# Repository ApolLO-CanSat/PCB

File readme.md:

# Team ApolLO's CanSat PCBs
The mainboard features:
- **RP2350A** MCU 
- **W25Q128JVPIQ** flash memory
- **Waveshare 23721** for GPS signal
- **RFM98W 433MHz** LoRa module
- **MPU-6050** gyroscope and accelerometer
- **BMP 280** barometer and thermometer
- **USB-C connector**
- **BOOTSEL** and **RESET** buttons
- Status **LED**
- **Buzzer** for easier recovery
\

\

\
[Schematics in PDF file](https://github.com/ApolLO-CanSat/PCB/blob/main/schematics/CanSat.pdf)
\

\
[PCB schematic in PDF file](https://github.com/ApolLO-CanSat/PCB/blob/main/schematics/CanSatPCB.pdf)
---
## BOM
|Id|Designator|Footprint|Quantity|Designation|
|-|-|-|-|-|
|1|R5,R24,R12,R1,R21,R23,R22|R_0805_2012Metric|7|10K|
|2|R26,R25|R_0402_1005Metric|2|4.7K|
|3|C25|C_0805_2012Metric|1|10nF|
|4|R4,R3|R_0805_2012Metric|2|27|
|5|J8|PinHeader_1x02_P2.00mm_Vertical|1|Conn_01x02_Pin|
|6|L1|AOTAB201610S3R3101T|1|3.3u|
|7|D2|LED_0402_1005Metric|1|RED|
|8|U5|RP2350-QFN-60-1EP_7x7_P0.4mm_EP3.4x3.4mm_ThermalVias|1|RP2350_60QFN|
|9|C16,C9,C8,C11|C_0402_1005Metric|4|4.7uF|
|10|C20,C3,C4,C10,C22,C12,C7,C1,C5,C6,C2|C_0402_1005Metric|11|100nF|
|11|C24,C23|C_0402_1005Metric|2|15pF|
|12|C30,C15,C17,C32,C27,C28,C19|C_0805_2012Metric|7|100nF|
|13|BZ1|CMT-4023S|1|Buzzer|
|14|J1|USB_C_Receptacle_Amphenol_12401610E4-2A|1|USB_C_Receptacle|
|15|C31|C_0805_2012Metric|1|22u|
|16|SW2,SW1,SW3|SW_Push_1P1T_NO_Vertical_Wuerth_434133025816|3|SW_Push|
|17|IC1|SON127P600X500X80-9N-D|1|W25Q128JVPIQ|
|18|C21,C13|C_0805_2012Metric|2|1uF|
|19|D1|MMBT2907AM3T5G|1|ESD7L5.0DT5G|
|20|D4,D3|D_SOD-123|2|MBR0530T1G|
|21|R11,R10|R_0805_2012Metric|2|5.1K|
|22|J10|PinHeader_1x04_P2.00mm_Vertical|1|Conn_01x04_Pin|
|23|R18|R_0805_2012Metric|1|100|
|24|J2|SMA_Amphenol_901-144_Vertical|1|Conn_Coaxial|
|25|R17|R_0402_1005Metric|1|10K|
|26|R20|R_0402_1005Metric|1|33|
|27|U3|PinHeader_1x05_P1.00mm_Vertical|1|Waveshare23721|
|28|C18|C_0805_2012Metric|1|2.2nF|
|29|U8|Bosch_LGA-8_2x2.5mm_P0.65mm_ClockwisePinNumbering|1|BMP280|
|30|R2,R14,R13|R_0805_2012Metric|3|1K|
|31|Y1|ABM8272T3|1|ABM8272T3|
|32|C29|C_0805_2012Metric|1|2.2uF|
|33|Q1|SOT-23|1|BSS138|
|34|U9|PSON50P200X300X50-9N|1|APS6404L-3SQR-ZR|
|35|J6|PinHeader_2x03_P1.00mm_Vertical|1|Conn_01x06_Pin|
|36|R15|R_0805_2012Metric|1|220|
|37|J7|JST_SH_BM03B-SRSS-TB_1x03-1MP_P1.00mm_Vertical|1|Conn_01x03_Pin|
|38|R16|R_0805_2012Metric|1|DNC|
|39|J5|JST_PH_B2B-PH-K_1x02_P2.00mm_Vertical|1|Screw_Terminal_01x02|
|40|J9|JST_SH_BM03B-SRSS-TB_1x03-1MP_P1.00mm_Vertical|1|Conn_01x02_Pin|
|41|J11|JST_PH_B3B-PH-K_1x03_P2.00mm_Vertical|1|Conn_01x03_Socket|
|42|J3|JST_SH_BM06B-SRSS-TB_1x06-1MP_P1.00mm_Vertical|1|Conn_01x06_Socket|
|43|U4|HOPERF_RFM9XW_SMD|1|RFM98W-433S2|
|44|C14|C_0805_2012Metric|1|DNP|
|45|U1|InvenSense_QFN-24_4x4mm_P0.5mm|1|MPU-6050|
|46|J4|JST_PH_B2B-PH-K_1x02_P2.00mm_Vertical|1|Conn_01x02_Pin|
|47|R19|R_0402_1005Metric|1|1K|

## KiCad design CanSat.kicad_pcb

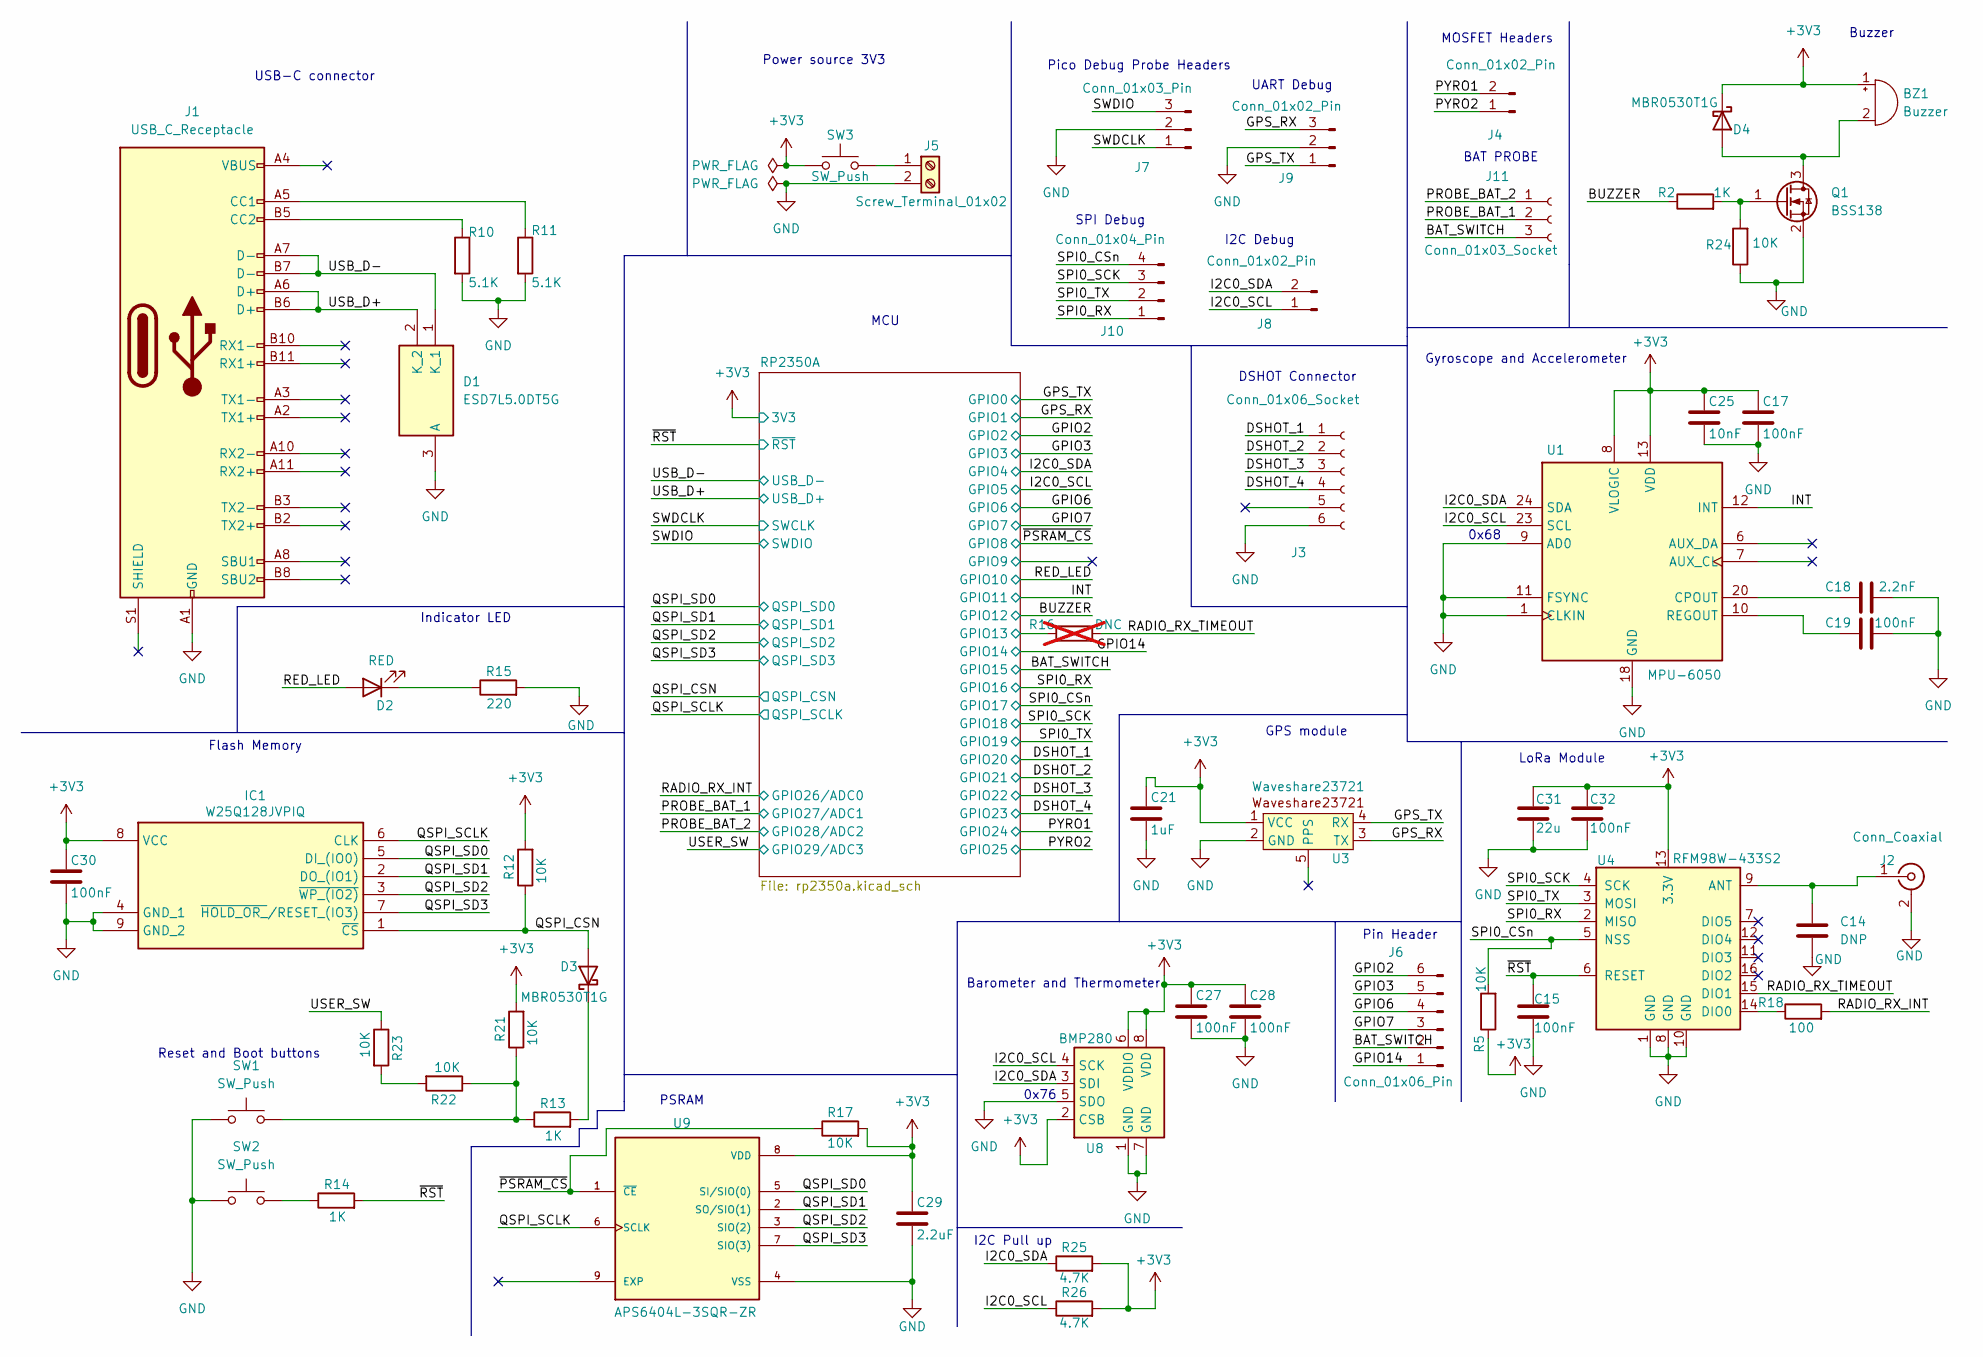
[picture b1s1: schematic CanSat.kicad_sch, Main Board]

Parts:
BZ1: Buzzer; CMT-4023S
C14: DNP; C_0805_2012Metric
C15, C17, C19, C27, C28, C30, C32: 100nF; C_0805_2012Metric
C18: 2.2nF; C_0805_2012Metric
C21: 1uF; C_0805_2012Metric
C25: 10nF; C_0805_2012Metric
C29: 2.2uF; C_0805_2012Metric
C31: 22u; C_0805_2012Metric
D1: ESD7L5.0DT5G; MMBT2907AM3T5G; Mouser Part Number 863-ESD7L5.0DT5G
D2: RED; LED_0402_1005Metric
D3, D4: MBR0530T1G; D_SOD-123
IC1: W25Q128JVPIQ; SON127P600X500X80-9N-D; Mouser Part Number 454-W25Q128JVPIQ
J1: USB_C_Receptacle; USB_C_Receptacle_Amphenol_12401610E4-2A
J2: Conn_Coaxial; SMA_Amphenol_901-144_Vertical
J3: Conn_01x06_Socket; JST_SH_BM06B-SRSS-TB_1x06-1MP_P1.00mm_Vertical
J4: Conn_01x02_Pin; JST_PH_B2B-PH-K_1x02_P2.00mm_Vertical
J5: Screw_Terminal_01x02; JST_PH_B2B-PH-K_1x02_P2.00mm_Vertical
J6: Conn_01x06_Pin; PinHeader_2x03_P1.00mm_Vertical
J7: Conn_01x03_Pin; JST_SH_BM03B-SRSS-TB_1x03-1MP_P1.00mm_Vertical
J8: Conn_01x02_Pin; PinHeader_1x02_P2.00mm_Vertical
J9: Conn_01x02_Pin; JST_SH_BM03B-SRSS-TB_1x03-1MP_P1.00mm_Vertical
J10: Conn_01x04_Pin; PinHeader_1x04_P2.00mm_Vertical
J11: Conn_01x03_Socket; JST_PH_B3B-PH-K_1x03_P2.00mm_Vertical
Q1: BSS138; SOT-23
R2, R13, R14: 1K; R_0805_2012Metric
R5, R12, R21, R22, R23, R24: 10K; R_0805_2012Metric
R10, R11: 5.1K; R_0805_2012Metric
R15: 220; R_0805_2012Metric
R16: DNC; R_0805_2012Metric; not fitted
R17: 10K; R_0402_1005Metric
R18: 100; R_0805_2012Metric
R25, R26: 4.7K; R_0402_1005Metric
SW1, SW2, SW3: SW_Push; SW_Push_1P1T_NO_Vertical_Wuerth_434133025816
U1: MPU-6050; InvenSense_QFN-24_4x4mm_P0.5mm
U3: Waveshare23721; PinHeader_1x05_P1.00mm_Vertical
U4: RFM98W-433S2; HOPERF_RFM9XW_SMD
U8: BMP280; Bosch_LGA-8_2x2.5mm_P0.65mm_ClockwisePinNumbering
U9: APS6404L-3SQR-ZR; PSON50P200X300X50-9N; PARTREV 2.3

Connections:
+3V3: BZ1.1 (+), C17.1, C21.1, C25.1, C27.1, C28.1, C29.1, C30.1, C31.1, C32.1, D4.1 (K), IC1.8 (VCC), R5.1, R12.2, R17.2, R21.2, R25.2, R26.2, SW3.1, U1.8 (VLOGIC), U1.13 (VDD), U3.1 (VCC), U4.13 (3.3V), U8.2 (CSB), U8.6 (VDDIO), U8.8 (VDD), U9.8 (VDD); also elsewhere on the board
/BAT_SWITCH: J6.2, J11.3; also elsewhere on the board
/BUZZER: R2.1; also elsewhere on the board
/DSHOT_1: J3.1; also elsewhere on the board
/DSHOT_2: J3.2; also elsewhere on the board
/DSHOT_3: J3.3; also elsewhere on the board
/DSHOT_4: J3.4; also elsewhere on the board
/GPIO2: J6.6; also elsewhere on the board
/GPIO3: J6.5; also elsewhere on the board
/GPIO6: J6.4; also elsewhere on the board
/GPIO7: J6.3; also elsewhere on the board
/GPIO14: J6.1; also elsewhere on the board
/GPS_RX: J9.3, U3.3 (TX); also elsewhere on the board
/GPS_TX: J9.1, U3.4 (RX); also elsewhere on the board
/I2C0_SCL: J8.1, R26.1, U1.23 (SCL), U8.4 (SCK); also elsewhere on the board
/I2C0_SDA: J8.2, R25.1, U1.24 (SDA), U8.3 (SDI); also elsewhere on the board
/INT: U1.12 (INT); also elsewhere on the board
/PROBE_BAT_1: J11.2; also elsewhere on the board
/PROBE_BAT_2: J11.1; also elsewhere on the board
/PYRO1: J4.2; also elsewhere on the board
/PYRO2: J4.1; also elsewhere on the board
/QSPI_CSN: D3.2 (A), IC1.1 (~CS), R12.1; also elsewhere on the board
/QSPI_SCLK: IC1.6 (CLK), U9.6 (SCLK); also elsewhere on the board
/QSPI_SD0: IC1.5 (DI_(IO0)), U9.5 (SI/SIO(0)); also elsewhere on the board
/QSPI_SD1: IC1.2 (DO_(IO1)), U9.2 (SO/SIO(1)); also elsewhere on the board
/QSPI_SD2: IC1.3 (~WP_(IO2)), U9.3 (SIO(2)); also elsewhere on the board
/QSPI_SD3: IC1.7 (~HOLD_OR_/RESET_(IO3)), U9.7 (SIO(3)); also elsewhere on the board
/RADIO_RX_INT: R18.2; also elsewhere on the board
/RADIO_RX_TIMEOUT: R16.2, U4.15 (DIO1)
/RED_LED: D2.2 (A); also elsewhere on the board
/RP2350A/GPIO13: R16.1; also elsewhere on the board
/SPI0_CSn: J10.4, R5.2, U4.5 (NSS); also elsewhere on the board
/SPI0_RX: J10.1, U4.2 (MISO); also elsewhere on the board
/SPI0_SCK: J10.3, U4.4 (SCK); also elsewhere on the board
/SPI0_TX: J10.2, U4.3 (MOSI); also elsewhere on the board
/SWDCLK: J7.1; also elsewhere on the board
/SWDIO: J7.3; also elsewhere on the board
/USB_D+: D1.2 (K_2), J1.A6 (D+), J1.B6 (D+); also elsewhere on the board
/USB_D-: D1.1 (K_1), J1.A7 (D-), J1.B7 (D-); also elsewhere on the board
/USER_SW: R23.1; also elsewhere on the board
/~PSRAM_CS: R17.1, U9.1 (~CE); also elsewhere on the board
/~RST: C15.1, R14.2, U4.6 (RESET); also elsewhere on the board
GND: C14.1, C15.2, C17.2, C18.2, C19.2, C21.2, C25.2, C27.2, C28.2, C29.2, C30.2, C31.2, C32.2, D1.3 (A), IC1.4 (GND_1), IC1.9 (GND_2), J1.A1 (GND), J1.A12 (GND), J1.B1 (GND), J1.B12 (GND), J2.2 (Ext), J3.6, J5.2, J7.2, J9.2, Q1.2 (S), R10.2, R11.2, R15.2, R24.1, SW1.1, SW2.1, U1.1 (CLKIN), U1.9 (AD0), U1.11 (FSYNC), U1.18 (GND), U3.2 (GND), U4.1 (GND), U4.8 (GND), U4.10 (GND), U8.1 (GND), U8.5 (SDO), U8.7 (GND), U9.4 (VSS); also elsewhere on the board
unnamed: BZ1.2 (-), D4.2 (A), Q1.3 (D)
unnamed: D2.1 (K), R15.1
unnamed: D3.1 (K), R13.2
unnamed: J1.A5 (CC1), R11.1
unnamed: J1.B5 (CC2), R10.1
unnamed: C14.2, J2.1 (In), U4.9 (ANT)
unnamed: J5.1, SW3.2
unnamed: Q1.1 (G), R2.2, R24.2
unnamed: R13.1, R21.1, R22.1, SW1.2
unnamed: R14.1, SW2.2
unnamed: R22.2, R23.2
unnamed: C18.1, U1.20 (CPOUT)
unnamed: C19.1, U1.10 (REGOUT)
unnamed: R18.1, U4.14 (DIO0)

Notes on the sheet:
I2C Pull up
0x68
BAT PROBE
UART Debug
Buzzer
Gyroscope and Accelerometer
Reset and Boot buttons
GPS module
LoRa Module
MOSFET Headers
Power source 3V3
Pin Header
I2C Debug
PSRAM
Pico Debug Probe Headers
MCU
0x76
SPI Debug
Barometer and Thermometer
USB-C connector
Indicator LED
Flash Memory
DSHOT Connector

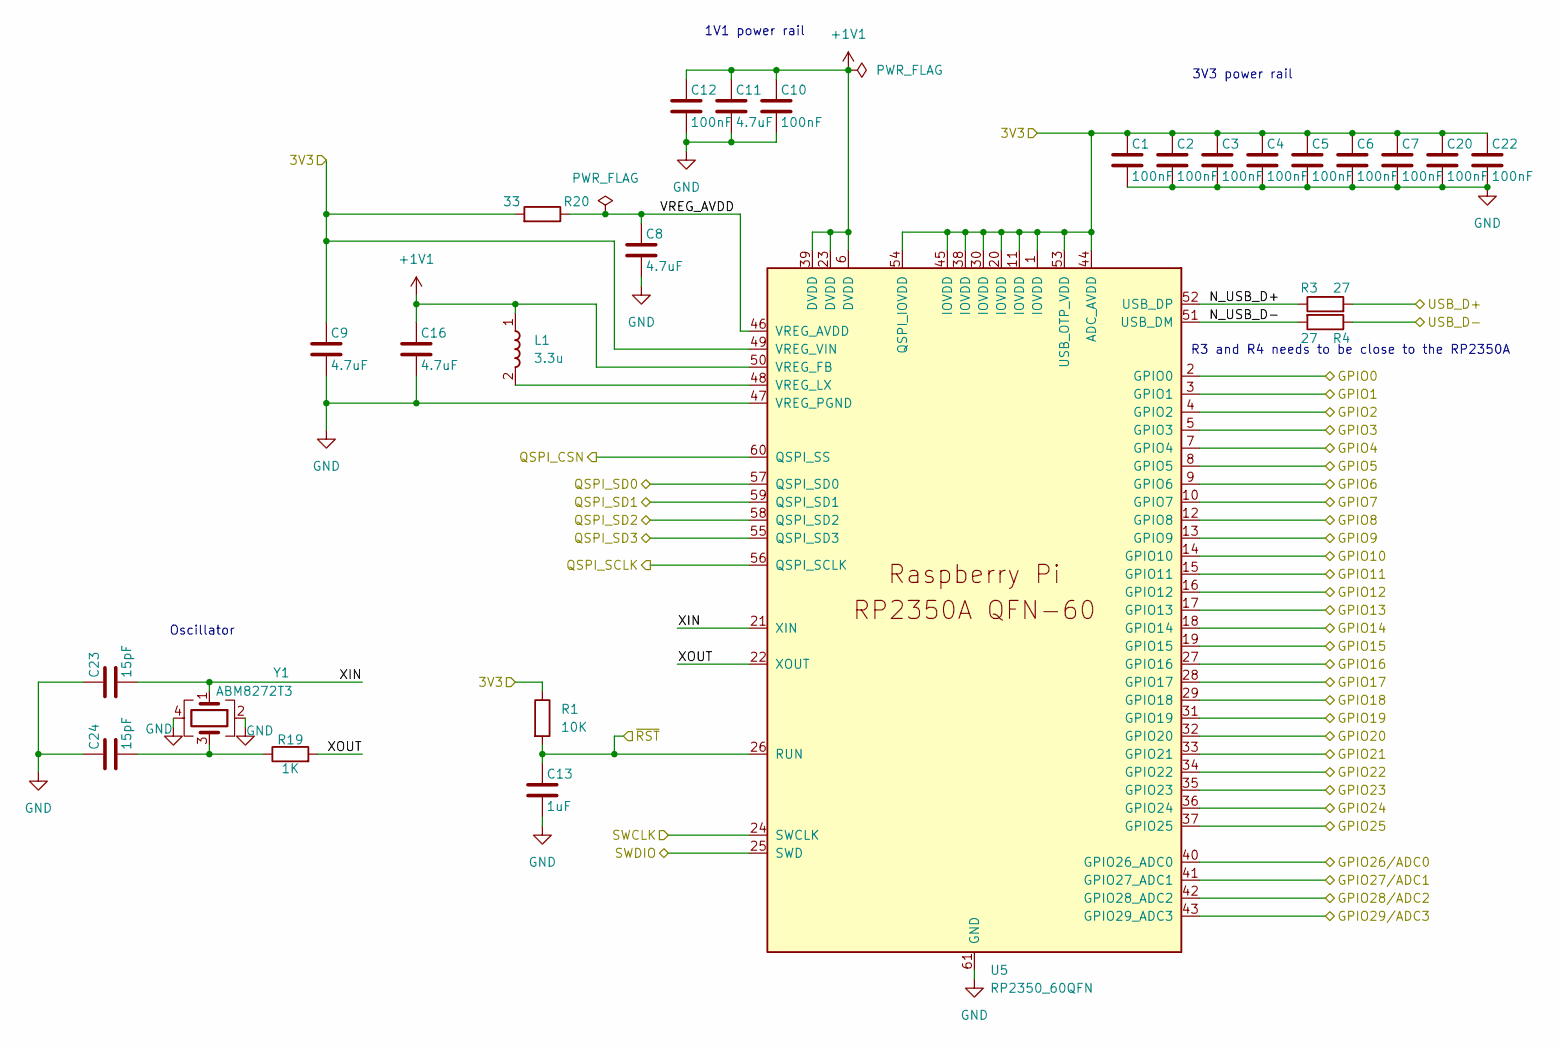
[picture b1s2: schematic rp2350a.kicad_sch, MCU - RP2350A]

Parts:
C1, C2, C3, C4, C5, C6, C7, C10, C12, C20, C22: 100nF; C_0402_1005Metric
C8, C9, C11, C16: 4.7uF; C_0402_1005Metric
C13: 1uF; C_0805_2012Metric
C23, C24: 15pF; C_0402_1005Metric
L1: 3.3u; AOTAB201610S3R3101T; Mouser Part Number 815-AB201610S3R3101T
R1: 10K; R_0805_2012Metric
R3, R4: 27; R_0805_2012Metric
R19: 1K; R_0402_1005Metric
R20: 33; R_0402_1005Metric
U5: RP2350_60QFN; RP2350-QFN-60-1EP_7x7_P0.4mm_EP3.4x3.4mm_ThermalVias
Y1: ABM8272T3

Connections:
+1V1: C10.1, C11.1, C12.1, C16.1, L1.1, U5.6 (DVDD), U5.23 (DVDD), U5.39 (DVDD), U5.50 (VREG_FB)
+3V3: C1.1, C2.1, C3.1, C4.1, C5.1, C6.1, C7.1, C9.1, C20.1, C22.1, R1.1, R20.2, U5.1 (IOVDD), U5.11 (IOVDD), U5.20 (IOVDD), U5.30 (IOVDD), U5.38 (IOVDD), U5.44 (ADC_AVDD), U5.45 (IOVDD), U5.49 (VREG_VIN), U5.53 (USB_OTP_VDD), U5.54 (QSPI_IOVDD); also elsewhere on the board
/BAT_SWITCH: U5.19 (GPIO15); also elsewhere on the board
/BUZZER: U5.16 (GPIO12); also elsewhere on the board
/DSHOT_1: U5.32 (GPIO20); also elsewhere on the board
/DSHOT_2: U5.33 (GPIO21); also elsewhere on the board
/DSHOT_3: U5.34 (GPIO22); also elsewhere on the board
/DSHOT_4: U5.35 (GPIO23); also elsewhere on the board
/GPIO2: U5.4 (GPIO2); also elsewhere on the board
/GPIO3: U5.5 (GPIO3); also elsewhere on the board
/GPIO6: U5.9 (GPIO6); also elsewhere on the board
/GPIO7: U5.10 (GPIO7); also elsewhere on the board
/GPIO14: U5.18 (GPIO14); also elsewhere on the board
/GPS_RX: U5.3 (GPIO1); also elsewhere on the board
/GPS_TX: U5.2 (GPIO0); also elsewhere on the board
/I2C0_SCL: U5.8 (GPIO5); also elsewhere on the board
/I2C0_SDA: U5.7 (GPIO4); also elsewhere on the board
/INT: U5.15 (GPIO11); also elsewhere on the board
/PROBE_BAT_1: U5.41 (GPIO27_ADC1); also elsewhere on the board
/PROBE_BAT_2: U5.42 (GPIO28_ADC2); also elsewhere on the board
/PYRO1: U5.36 (GPIO24); also elsewhere on the board
/PYRO2: U5.37 (GPIO25); also elsewhere on the board
/QSPI_CSN: U5.60 (QSPI_SS); also elsewhere on the board
/QSPI_SCLK: U5.56 (QSPI_SCLK); also elsewhere on the board
/QSPI_SD0: U5.57 (QSPI_SD0); also elsewhere on the board
/QSPI_SD1: U5.59 (QSPI_SD1); also elsewhere on the board
/QSPI_SD2: U5.58 (QSPI_SD2); also elsewhere on the board
/QSPI_SD3: U5.55 (QSPI_SD3); also elsewhere on the board
/RADIO_RX_INT: U5.40 (GPIO26_ADC0); also elsewhere on the board
/RED_LED: U5.14 (GPIO10); also elsewhere on the board
/RP2350A/GPIO9: U5.13 (GPIO9)
/RP2350A/GPIO13: U5.17 (GPIO13); also elsewhere on the board
/RP2350A/N_USB_D+: R3.1, U5.52 (USB_DP)
/RP2350A/N_USB_D-: R4.2, U5.51 (USB_DM)
/RP2350A/VREG_AVDD: C8.1, R20.1, U5.46 (VREG_AVDD)
/RP2350A/XIN: C23.2, U5.21 (XIN), Y1.1
/RP2350A/XOUT: R19.2, U5.22 (XOUT)
/SPI0_CSn: U5.28 (GPIO17); also elsewhere on the board
/SPI0_RX: U5.27 (GPIO16); also elsewhere on the board
/SPI0_SCK: U5.29 (GPIO18); also elsewhere on the board
/SPI0_TX: U5.31 (GPIO19); also elsewhere on the board
/SWDCLK: U5.24 (SWCLK); also elsewhere on the board
/SWDIO: U5.25 (SWD); also elsewhere on the board
/USB_D+: R3.2; also elsewhere on the board
/USB_D-: R4.1; also elsewhere on the board
/USER_SW: U5.43 (GPIO29_ADC3); also elsewhere on the board
/~PSRAM_CS: U5.12 (GPIO8); also elsewhere on the board
/~RST: C13.1, R1.2, U5.26 (RUN); also elsewhere on the board
GND: C1.2, C2.2, C3.2, C4.2, C5.2, C6.2, C7.2, C8.2, C9.2, C10.2, C11.2, C12.2, C13.2, C16.2, C20.2, C22.2, C23.1, C24.1, U5.47 (VREG_PGND), U5.61 (GND), Y1.2, Y1.4; also elsewhere on the board
unnamed: C24.2, R19.1, Y1.3
unnamed: L1.2, U5.48 (VREG_LX)

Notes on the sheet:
1V1 power rail
R3 and R4 needs to be close to the RP2350A
3V3 power rail
Oscillator

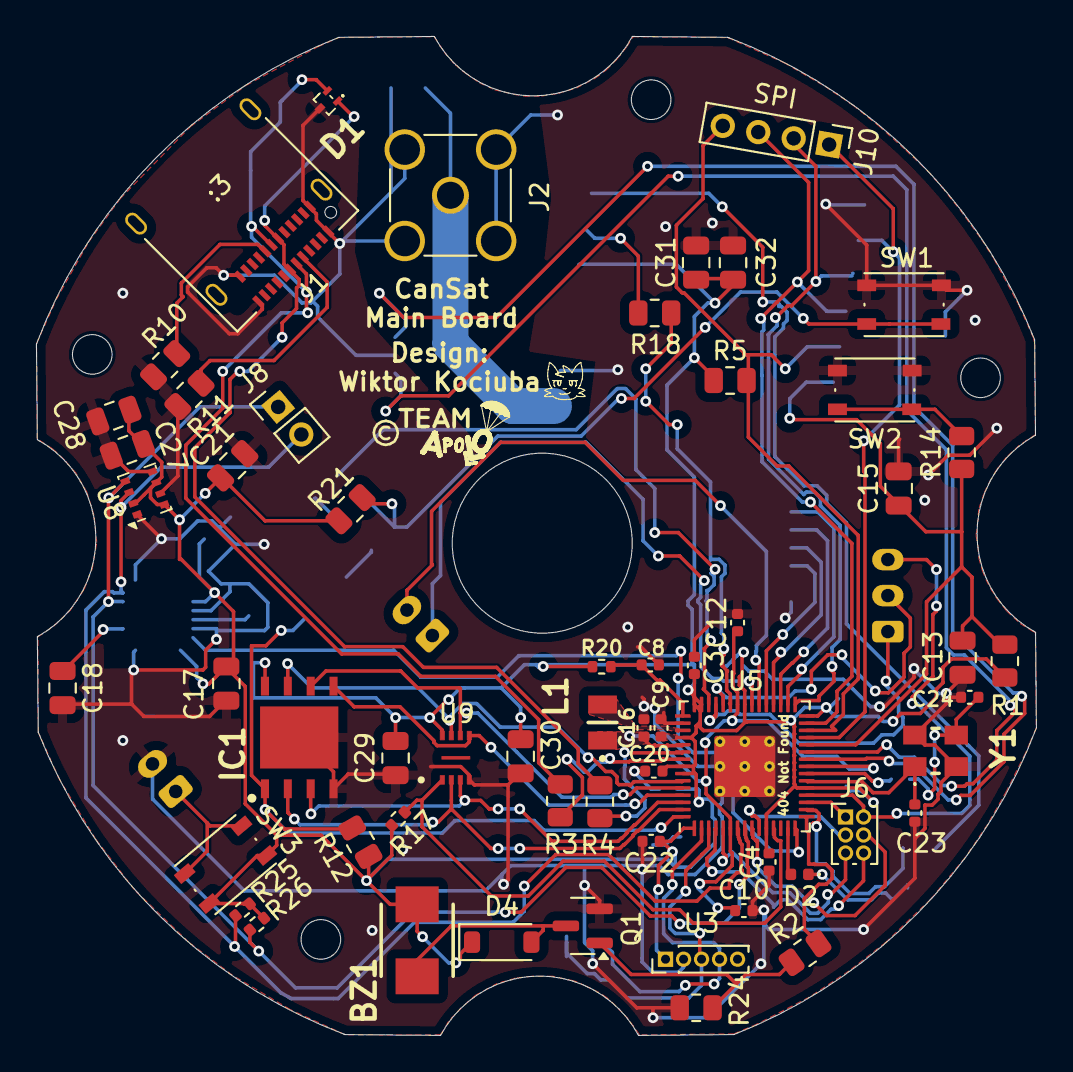
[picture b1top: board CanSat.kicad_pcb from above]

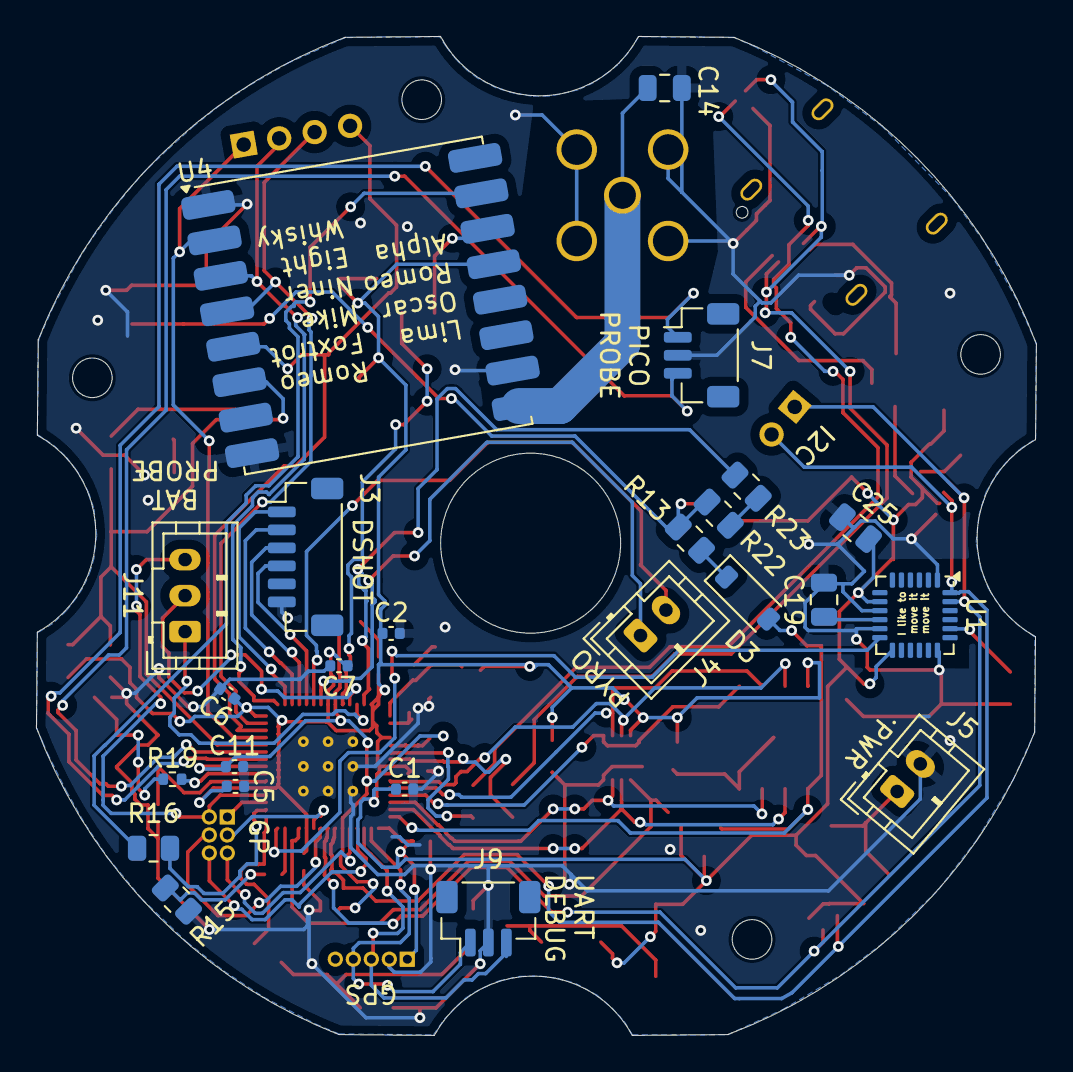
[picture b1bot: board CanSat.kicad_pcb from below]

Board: 2 copper layers, 55.6 x 55.5 mm, 84 parts (24 on the bottom side), 65 nets.

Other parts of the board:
M2, M2#2: MountingHole_2.2mm_M2

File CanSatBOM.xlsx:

Id | Designator | Footprint | Quantity | Value | Manufacturer | Mfg Part # | Package | Type
1 | R4,R7,R3,R8,R9,R6,R5 | R_0805_2012Metric | 7 | 27 OHM | any available | any available | 0805(2012M) | SMD
2 | J8,J9,J4 | PinHeader_1x02_P1.00mm_Vertical | 3 | n/a | any available | any available | PinHeader_1x02_P1.00mm_Vertical | THT
3 | D2 | LED_0402_1005Metric | 1 | RED | any available | any available | 0402(1005M) | SMD
4 | U5 | RP2350-QFN-60-1EP_7x7_P0.4mm_EP3.4x3.4mm_ThermalVias | 1 | n/a | Raspberry Pi | RP2350A | SMD | SMD
5 | C30,C27,C28,C3,C4,C7,C10,C1,C5,C6,C12,C2 | CP_EIA-2012-15_AVX-P | 12 | 100nF | any available | any available | 2012-15M | SMD
6 | R23,R22,R12,R1,R2,R21 | R_0805_2012Metric | 6 | 10K OHM | any available | any available | 0805(2012M) | SMD
7 | BZ1 | MagneticBuzzer_Kingstate_KCG0601 | 1 | n/a | Kingstate | KCG0601 | THT | THT
8 | J1 | USB_C_Receptacle_Amphenol_12401610E4-2A | 1 | n/a | Amphenol | 12401610E4#2A | SMD | SMD
9 | C31 | CP_EIA-2012-15_AVX-P | 1 | 22uF | any available | any available | 2012-15M | SMD
10 | L1 | L_6.3x6.3_H3 | 1 | 3.3uH | any available | any available | L_6.3x6.3_H3 | SMD
11 | SW2,SW1,SW3 | SW_Push_1P1T_NO_Vertical_Wuerth_434133025816 | 3 | n/a | Wuerth | 434133025816 | SMD | SMD
12 | C15,C32 | CP_EIA-2012-15_AVX-P | 2 | 100nF | any available | any available | 2012-15M | SMD
13 | IC1 | SON127P600X500X80-9N-D | 1 | n/a | Winbond | W25Q128JVPIQ | SMD | SMD
14 | C21,C13,C14 | CP_EIA-2012-15_AVX-P | 3 | 1uF | any available | any available | 2012-15M | SMD
15 | C17 | CP_EIA-2012-15_AVX-P | 1 | 0.1uF | any available | any available | 2012-15M | SMD
16 | D1 | MMBT2907AM3T5G | 1 | n/a | onsemi | ESD7L5.0DT5G | SMD | SMD
17 | J7 | PinHeader_1x03_P1.00mm_Vertical | 1 | Conn_01x03_Pin | any available | any available | PinHeader_1x03_P1.00mm_Vertical | THT
18 | R11,R10 | R_0805_2012Metric | 2 | 5.1K Ohm | any available | any available | 0805(2012M) | SMD
19 | J10 | PinHeader_1x04_P1.00mm_Vertical | 1 | Conn_01x04_Pin | any available | any available | PinHeader_1x04_P1.00mm_Vertical | THT
20 | R18 | R_0805_2012Metric | 1 | 100 Ohm | any available | any available | 0805(2012M) | SMD
21 | C9,C16,C8,C11 | CP_EIA-2012-15_AVX-P | 4 | 4.7uF | any available | any available | 2012-15M | SMD
22 | J2 | SMA_Amphenol_901-144_Vertical | 1 | DNC | DNC | DNC | DNC | DNC
23 | R20 | R_0805_2012Metric | 1 | 33 Ohm | any available | any available | 0805(2012M) | SMD
24 | U3 | PinHeader_1x05_P1.00mm_Vertical | 1 | Conn_01x05_Pin | any available | any available | PinHeader_1x05_P1.00mm_Vertical | THT
25 | C18,C19 | CP_EIA-2012-15_AVX-P | 2 | 2.2nF | any available | any available | 2012-15M | SMD
26 | Y2 | ASE12000MHzET | 1 | n/a | Abracon | ASE-12.000MHz-E-T | SMD | SMD
27 | U8 | Bosch_LGA-8_2x2.5mm_P0.65mm_ClockwisePinNumbering | 1 | n/a | Bosch | BMP280 | SMD | SMD
28 | C29 | CP_EIA-2012-15_AVX-P | 1 | 2.2uF | any available | any available | 2012-15M | SMD
29 | U9 | PSON50P200X300X50-9N | 1 | n/a | AP Memory | APS6404L-3SQR-ZR | SMD | SMD
30 | J6 | PinHeader_2x03_P1.00mm_Vertical | 1 | Conn_01x06_Pin | any available | any available | PinHeader_2x03_P1.00mm_Vertical | THT
31 | R14,R13 | R_0805_2012Metric | 2 | 1K Ohm | any available | any available | 0805(2012M) | SMD
32 | R15 | R_0805_2012Metric | 1 | 220 Ohm | any available | any available | 0805(2012M) | SMD
33 | R16 | R_0805_2012Metric | 1 | DNC | DNC | DNC | DNC | DNC
34 | J5 | TerminalBlock_bornier-2_P5.08mm | 1 | Screw_Terminal_01x02 | any available | any available | Screw_Terminal_01x02 | THT
35 | J3 | JST_SH_BM06B-SRSS-TB_1x06-1MP_P1.00mm_Vertical | 1 | Conn_01x06_Socket | JST | BM06B-SRSS-TB (LF)(SN) | SMD | SMD
36 | U4 | HOPERF_RFM9XW_SMD | 1 | n/a | RF Solutions | RFM98W-433S2 | SMD | SMD
37 | D3 | D_SOD-123 | 1 | n/a | onsemi | MBR0530 | SMD | SMD
38 | U1 | InvenSense_QFN-24_4x4mm_P0.5mm | 1 | n/a | InvenSense | MPU-6050 | SMD | SMD

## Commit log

2025-11-21 Add new flash memory and PSRAM
2025-11-21 Add new LoRa module
2025-11-21 Assigned footprints and drew pcb outline
2025-11-22 Add components to pcb
    Added:
    3V3 power source
    USB-C connector
    Flash memory and PSRAM
2025-12-10 Connected LoRa
2025-12-10 Added more components to the pcb
2025-12-10 Connected all components
2025-12-10 Rotated LoRa and updated readme
2025-12-15 Update of pcb
2026-01-17 Update LoRa module name in README
2026-01-22 Changed LoRa module to RFM98W 433MHz
2026-01-22 Fixed silkscreen overlap
2026-01-26 Added pin headers, debug headers, changed power source
2026-02-17 Added BOM to readme
2026-03-07 Changed LoRa footprint + signed the PCB + added a on/off button
2026-03-11 Fixed design flaw with with components that MCU depends on
2026-03-13 Changed connectors
2026-03-13 Readme Update
2026-03-13 changed buzzer circuit and capacitor footprints
2026-03-13 added Q1 part number
2026-03-13 Initial plan
2026-03-13 updated spacing
2026-03-13 Changed QSPI and added pull-ups on i2c
2026-03-26 Fixed USB data lines
